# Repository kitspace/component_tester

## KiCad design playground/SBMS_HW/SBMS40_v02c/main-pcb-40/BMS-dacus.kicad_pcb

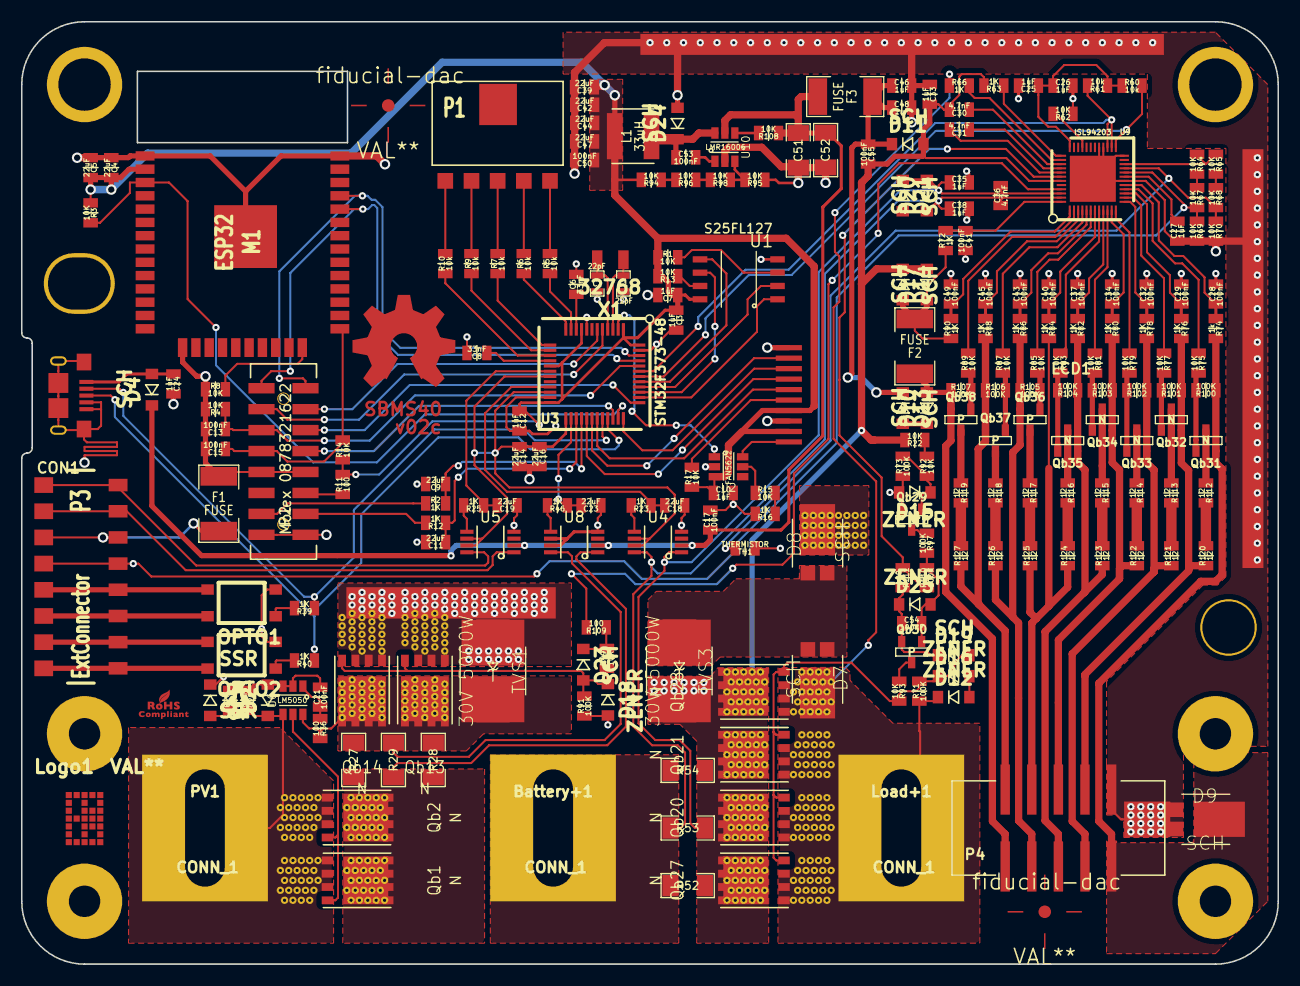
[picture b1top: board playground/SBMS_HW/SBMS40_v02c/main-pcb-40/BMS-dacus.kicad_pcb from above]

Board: 2 copper layers, 120.0 x 90.0 mm, 225 parts (0 on the bottom side), 164 nets.

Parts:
Battery+1: CONN_1; 1PIN_Power-dac-65A2
C1, C2: 22pF; SM0603_Capa
C3, C7, C10, C12, C24, C25, C26, C27, C33, C35, C38, C46, C48: 1uF; SM0805-dac
C4, C5, C9, C11, C14, C16, C18, C19, C23, C39, C42, C44, C47: 22uF; SM0805-dac
C6, C8: 33nF; SM0805-dac
C13, C15, C17, C20, C21, C28, C29, C32, C34, C37, C40, C41, C43, C45, C49, C50, C53, C54, C55: 100nF; SM0805-dac
C30, C31, C36: 4.7nF; SM0805-dac
C51, C52: 10uF; SM1206
CON1: USB-MICRO-B; USB_MICRO_B-2
D1, D2, D4, D10, D11, D13, D14, D17, D19, D20, D21, D23, D24: SCH; Diode-dac3
D7: SCH; SBRT20M80-dac-simple4-D7
D8: SCH; SBRT20M80-dac-simple4-D8
D9: SCH; SBRT20M80-dac-simple4-D9
D12, D15, D16, D18, D25: ZENER; Diode-dac3
F1, F2, F3: FUSE; SM1808-dac
L1: 33uH; 5x5-L1
LCD1: LCD-10pin; LCD-24-10pin
Load+1: CONN_1; 1PIN_Power-dac-65A2
Logo1: VAL**; Logo1
M1: ESP32; ESP32-2
OPTO1, OPTO2: SSR; Opto-dac3
OSHW_COPPER_10MM: VAL**; OSHW_COPPER_10MM
P1: TouchButtons; SIL-5-dac
P2: Molex 0878321622; con_8x2x2mm-dac
P3: ExtConnector; SMD-8-dac1
P4: CellMon; 5x2_SMD-dac
PV1: CONN_1; 1PIN_Power-dac-65A2
Qb1, Qb2, Qb13, Qb14, Qb20, Qb21, Qb27, Qb28: N; PG-TDSON-dac-vias3
Qb29, Qb31, Qb32, Qb33, Qb34, Qb35: N; SOT23-dac-4
Qb30, Qb36, Qb37, Qb38: P; SOT23-dac-4
R1, R3, R4, R8, R13, R14, R15, R17, R22, R62, R64, R65, R67, R68, R69, R70, R75, R77, R79, R81, R83, R85, R87, R89, R92, R93, R94, R95, R96, R98, R99, R108: 10K; SM0805-dac
R2, R12, R16, R20, R23, R25, R39, R40, R46, R63, R66, R72, R76, R78, R80, R82, R84, R86, R88, R90: 1K; SM0805-dac
R5, R6, R7, R9, R10, R60, R61: 10k; SM0805-dac
R11, R36, R109, R111: 100; SM0805-dac
R27, R28, R29, R52, R53, R54: 1mR; SM1206
R71, R73, R91, R97, R100, R101, R102, R103, R104, R105, R106, R107, R110: 100K; SM0805-dac
R74: 1k; SM0805-dac
R112, R113, R114, R115, R116, R117, R118, R119, R120, R121, R122, R123, R124, R125, R126, R127: 12; SM0805-dac
TH1: THERMISTOR; SM0805-dac
TVS1: 30V 5000W; DO-214AB-dac-simple4-TVS1
TVS3: 30V 5000W; DO-214AB-dac-simple4-TVS3
U1: S25FL127; Flash-SO8E-dac2
U2: FAN5622; LM5050-SOT23_6-dac
U3: STM32F373-48; LQFP48-3-dac
U4, U5, U8: LMP8481; LMP8481-SSOP8-dac
U6: LM5050; LM5050-SOT23_6-dac
U9: ISL94203; QFP48-dac-3
U10: LMR16006; LM5050-SOT23_6-dac
X1: 32768; 32khz
fiducial-dac: VAL**; fiducial-dac3
fiducial-dac#2: VAL**; fiducial-dac3

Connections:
/ADC1N: P3.1, U5.8
/ADC1P: P3.2, U5.1
/BAT0: D9.2, P4.2, Qb31.S, R74.2, R100.1
/BAT1: P4.3, Qb32.S, R76.2, R101.1, R120.1
/BAT2: P4.4, Qb33.S, R78.2, R102.1, R121.1
/BAT3: P4.5, Qb34.S, R80.2, R103.1, R122.1
/BAT4: P4.6, Qb35.S, R82.2, R104.1, R123.1
/BAT5: P4.7, R84.2, R124.1, R125.1
/BAT6: P4.8, Qb36.S, R86.2, R105.1, R126.1
/BAT7: P4.9, Qb37.S, R88.2, R106.1, R127.1
/BAT+: D10.1, F2.1, P4.10, Qb38.S, R107.1
/BOOT0: C13.1, P2.5, R4.1, U3.44
/CFET: R109.2, U9.45
/CFET1: D18.2, D23.1, Qb13.G, Qb14.G, R91.2, R99.1
/CPV1P: Qb1.D, Qb2.D, R27.1, R28.1, R29.1, U8.1
/CSI1a: Battery+1.1, C36.1, C38.1, D20.2, D21.1, R52.1, R53.1, R54.1, U4.8, U9.47
/CSI2a: C30.2, C33.2, C35.1, C36.2, C55.2, D11.1, D14.2, D17.1, D18.1, D20.1, D21.2, Qb13.S, Qb14.S, Qb20.D, Qb21.D, Qb27.D, Qb28.D, R22.2, R52.2, R53.2, R54.2, R63.2, R91.1, TVS1.1, TVS3.2, U4.1, U9.43, U9.46
/DFET: R110.1, R111.1, U9.42
/DFET1: D16.2, D19.1, Qb20.G, Qb21.G, Qb27.G, Qb28.G, R71.2, R93.2
/DG1: Qb1.G, Qb2.G, U6.5
/ESPFLASH: C15.1, M1.25, P2.7, R14.2
/ESPRST: M1.3, R3.2, U3.35
/EXTADC1: C19.2, R25.1, U3.18
/EXTADC2: C9.1, R2.2, U3.28
/EXTADC3: C11.1, R12.1, U3.27
/EXTIO1: P2.3, U3.5
/EXTIO2: P2.4, U3.6
/EXTIO3: CON1.2, R39.1, U3.32
/EXTIO4: CON1.3, R40.1, U3.33
/EXTIO5: P2.6, U3.37
/FBAT+: C17.1, C51.1, C52.1, D4.2, F3.2, R108.1, U4.2, U5.2, U8.2, U10.5
/GCB1: Qb31.G, R75.2, R100.2
/GCB2: Qb32.G, R77.2, R101.2
/GCB3: Qb33.G, R79.2, R102.2
/GCB4: Qb34.G, R81.2, R103.2
/GCB5: Qb35.G, R83.2, R104.2
/GCB6: Qb36.G, R85.1, R105.2
/GCB7: Qb37.G, R87.1, R106.2
/GCB8: Qb38.G, R89.1, R107.2
/LCDCS: LCD1.3, U3.36
/LCDDC: LCD1.2, U3.30
/LCDLED: U2.1, U3.2
/LCDSCLK: LCD1.4, U3.29
/LCDSDI: LCD1.5, U3.31
/LDMON: D7.2, D12.2, Load+1.1, Qb20.S, Qb21.S, Qb27.S, Qb28.S, R66.1, R71.1
/PA1: P1.1, R10.2
/PA2: P1.2, R9.2
/PA3: P1.3, R7.2
/PA4: P1.4, R6.2
/PA5: P1.5, R5.2
/PV1: C20.2, D2.2, PV1.1, Qb1.S, Qb2.S, U6.4
/PV+: Qb13.D, Qb14.D, R27.2, R28.2, R29.2, R36.2, TVS1.2, U6.6, U8.8
/SCK: R60.2, U3.42, U9.25
/SDA: R61.2, U3.43, U9.26, U9.27
/SDADC2P: C18.2, R23.1, U3.21
/SDADC38: C23.2, R46.1, U3.26
/SPI1CLK: U1.6, U3.39
/SPI1CS: U1.1, U3.38
/SPI1MISO: U1.2, U3.40
/SPI1MOSI: U1.5, U3.41
/SWD: P2.8, U3.34
/TEMPO: R64.1, R65.1, U9.22
/USARTRX: M1.35, P2.2, U3.46
/USARTTX: M1.34, P2.1, U3.45
/VBATT: C41.1, R72.2, U9.48
/VC0: C28.1, R74.1, U9.17
/VC1: C29.1, R76.1, U9.15
/VC2: C32.1, R78.1, U9.13
/VC3: C34.1, R80.1, U9.11
/VC4: C37.1, R82.1, U9.9
/VC5: C40.1, R84.1, U9.7
/VC6: C43.1, R86.1, U9.5
/VC7: C45.1, R88.1, U9.3
/VC8: C49.1, R90.2, U9.1
/VDD33: C3.1, C4.2, C5.2, C7.1, C10.1, C12.1, C39.1, C42.1, C44.1, C47.1, C50.1, L1.1, LCD1.7, LCD1.9, M1.2, R1.1, R3.1, R11.2, R13.2, R14.1, R17.1, R94.2, U1.8, U2.3, U3.1, U3.9, U3.17, U3.24, U3.48
/VREFSD: C14.1, C16.1, U3.19, U3.22, U3.25, U4.6, U4.7, U5.6, U5.7
/XT1: P3.4, R67.2, R69.1, U9.20
/XT2: R68.2, R70.1, TH1.2, U9.21
GND: C1.2, C2.1, C3.2, C4.1, C5.1, C6.2, C7.2, C8.2, C9.2, C10.2, C11.2, C12.2, C13.2, C14.2, C15.2, C16.2, C17.2, C18.1, C19.1, C23.1, C24.2, C25.2, C26.2, C27.1, C28.2, C29.2, C32.2, C33.1, C34.2, C35.2, C37.2, C38.2, C39.2, C40.2, C41.2, C42.2, C43.2, C44.2, C45.2, C46.2, C47.2, C48.2, C49.2, C50.2, C51.2, C52.2, CON1.4, CON1.5, CON1.6, CON1.7, CON1.8, CON1.9, D1.2, D8.2, D9.1, D15.1, D24.1, F1.1, LCD1.1, LCD1.8, M1.1, M1.15, M1.38, M1.39, OPTO1.2, OPTO2.2, P2.9, P2.10, P2.15, P2.16, P4.1, Qb29.S, R4.2, R8.1, R16.2, R62.1, R69.2, R70.2, R73.1, R95.1, TH1.1, U1.4, U2.2, U3.8, U3.23, U3.47, U4.4, U5.4, U8.4, U8.6, U8.7, U9.0, U9.18, U9.24, U9.28, U9.29, U10.2
unnamed: C1.1, U3.3, X1.2
unnamed: C2.2, U3.4, X1.1
unnamed: C6.1, U3.10
unnamed: C8.1, U3.16
unnamed: C20.1, C21.2, D2.1, R20.2, U6.2, U6.3
unnamed: C21.1, R36.1, U6.1
unnamed: C24.1, CON1.1, D4.1
unnamed: C25.1, C26.1, R60.1, R61.1, U9.36
unnamed: C27.2, U9.19
unnamed: C30.1, U9.39
unnamed: C31.1, U9.40
unnamed: C31.2, U9.41
unnamed: C46.1, C48.1, C55.1, D11.2, D13.2, F3.1
unnamed: C53.1, D24.2, L1.2, U10.6
unnamed: C53.2, U10.1
unnamed: C54.1, D19.2, D25.2, Qb30.S, R111.2
unnamed: C54.2, D25.1, Qb30.G, R97.2, R110.2
unnamed: D1.1, R20.1
unnamed: D7.1, D8.1, TVS3.1
unnamed: D10.2, D13.1
unnamed: D12.1, D16.1
unnamed: D14.1, D17.2, F2.2, R72.1, R90.1
unnamed: D15.2, Qb29.G, R73.2, R92.1
unnamed: D23.2, R99.2, R109.1
unnamed: F1.2, P3.3
unnamed: LCD1.6, R17.2
unnamed: LCD1.10, U2.6
unnamed: M1.24, R8.2
unnamed: OPTO1.1, R39.2
unnamed: OPTO1.3, P3.5
unnamed: OPTO1.4, P3.6
unnamed: OPTO2.1, R40.2
unnamed: OPTO2.3, P3.7
unnamed: OPTO2.4, P3.8
unnamed: P2.12, R11.1
unnamed: P2.13, R2.1
unnamed: P2.14, R12.2
unnamed: Qb29.D, R97.1
unnamed: Qb30.D, R93.1
unnamed: Qb31.D, R112.1
unnamed: Qb32.D, R113.1
unnamed: Qb33.D, R114.1
unnamed: Qb34.D, R115.1
unnamed: Qb35.D, R116.1
unnamed: Qb36.D, R117.1
unnamed: Qb37.D, R118.1
unnamed: Qb38.D, R119.1
unnamed: R1.2, U1.3
unnamed: R5.1, U3.11
unnamed: R6.1, U3.12
unnamed: R7.1, U3.13
unnamed: R9.1, U3.14
unnamed: R10.1, U3.15
unnamed: R13.1, U1.7
unnamed: R15.1, U2.5
unnamed: R15.2, R16.1
unnamed: R22.1, R92.2
unnamed: R23.2, U4.5
unnamed: R25.2, U5.5
unnamed: R46.2, U8.5
unnamed: R62.2, U9.33
unnamed: R63.1, U9.37
unnamed: R64.2, R67.1
unnamed: R65.2, R68.1
unnamed: R66.2, U9.38
unnamed: R75.1, U9.16
unnamed: R77.1, U9.14
unnamed: R79.1, U9.12
unnamed: R81.1, U9.10
unnamed: R83.1, U9.8
unnamed: R85.2, U9.6
unnamed: R87.2, U9.4
unnamed: R89.2, U9.2
unnamed: R94.1, R96.2
unnamed: R95.2, R98.1, U10.3
unnamed: R96.1, R98.2
unnamed: R108.2, U10.4
unnamed: R112.2, R120.2
unnamed: R113.2, R121.2
unnamed: R114.2, R122.2
unnamed: R115.2, R123.2
unnamed: R116.2, R124.2
unnamed: R117.2, R125.2
unnamed: R118.2, R126.2
unnamed: R119.2, R127.2

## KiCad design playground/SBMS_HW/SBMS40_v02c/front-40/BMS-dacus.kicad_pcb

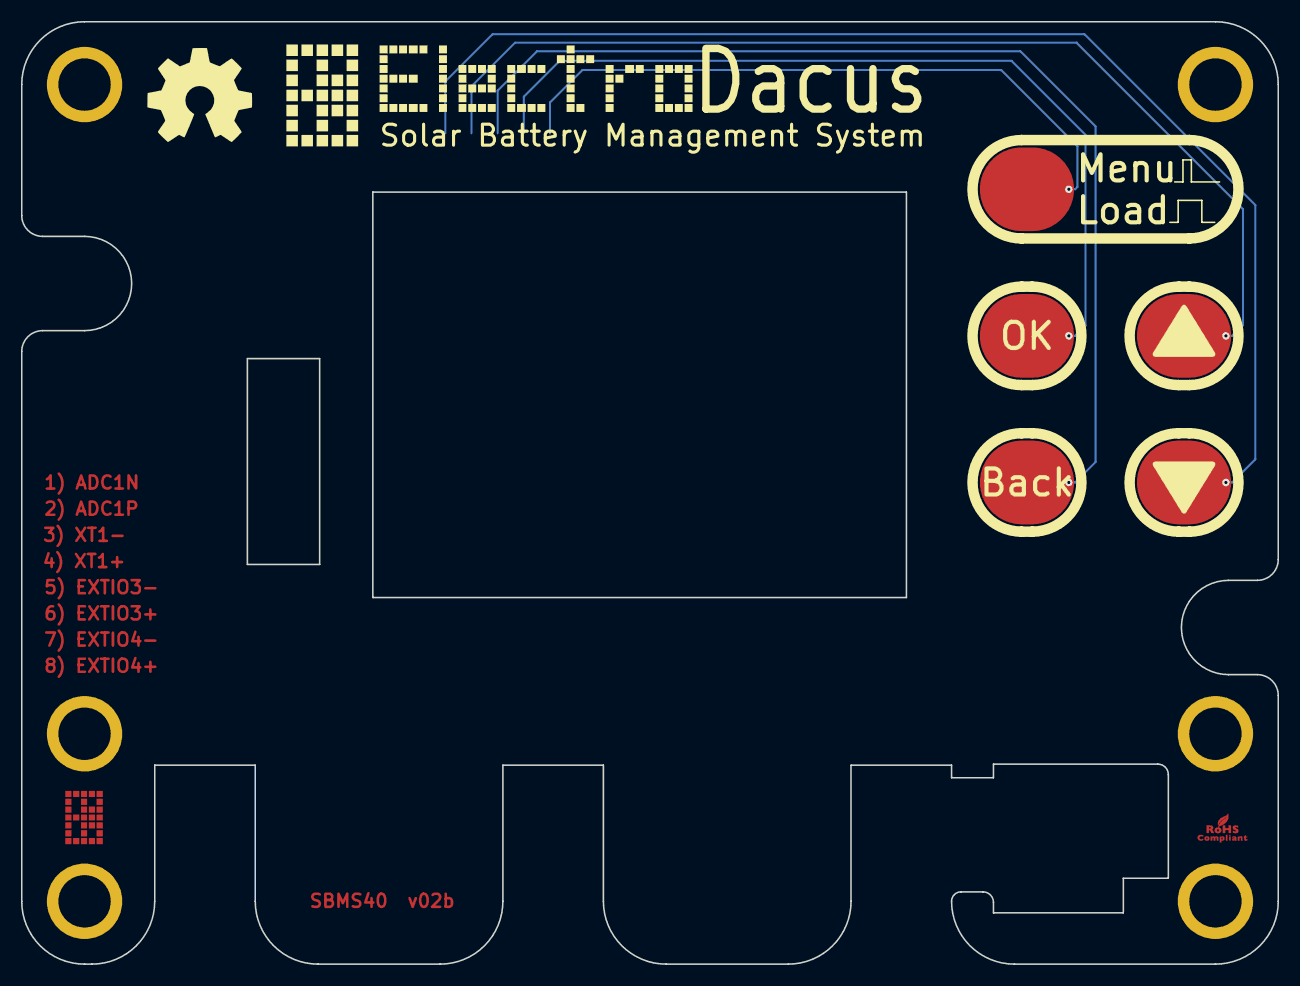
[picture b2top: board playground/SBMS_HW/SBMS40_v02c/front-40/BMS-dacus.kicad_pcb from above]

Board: 2 copper layers, 120.0 x 90.0 mm, 11 parts (0 on the bottom side), 5 nets.

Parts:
BA1, BA2, BA3, BA4, BA5: CONN_1; button_SMD-dac-40
Logo1: VAL**; Logo1
PA1, PA2, PA3, PA4, PA5: CONN_1; button_contact_SMD-dac3

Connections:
unnamed: BA1.1, PA1.1
unnamed: BA2.1, PA2.1
unnamed: BA3.1, PA3.1
unnamed: BA4.1, PA4.1
unnamed: BA5.1, PA5.1

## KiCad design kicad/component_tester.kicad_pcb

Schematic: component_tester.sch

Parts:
DRAWING101: DRAWING; combined

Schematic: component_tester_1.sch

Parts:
BAT201: CR2032; Battery_Retainer_2032_BK-912
C201: 10uF; C_0805
C202: 100n; C_0402
C203, C207: 47u; C_0805
C204, C205: 22p; C_0201
C206: 1n; C_0201
C208, C209, C210, C211, C212, C213: V 3p; C_0201
D201: BAV99; SOT-523; MPN1 BAV99T-7-F
D203: BAS40; LED_0402; MPN BAS40LP-7
DRAWING201: DRAWING; pads
DRAWING202: DRAWING; pads_bottom
IC201: MCP1640; SOT23-6
IC202: ATmega328P-MMH; QFN-28-1EP_4x4mm_Pitch0.4mm
L201: 4.7uH; R_0603
Q201: 8 MHz; NDK-NX3225GA_xtal
R201, R202, R203, R205, R210, R211, R212, R213: 10k; R_0201
R204: 1M; R_0201
R206: 750k; R_0201
R207: 240k; R_0201
R209: 330k; R_0201
R214, R216, R218: 680; R_0201
R215, R217, R219: 470k; R_0201
SW201: EVQ; PANASONIC_EVQ
T201: PMV65XP; SOT23
T202: BSS84; SOT23
T203: BSS123; SOT-323_SC-70; MPN BSS123W-7-F
T204: BC847; SOT-523; MPN BC847AT-7-F
X201: MICRO-USB; TE_1981568-1
X202: ISP; Pin_Header_Straight_2x03_Pitch1.27mm

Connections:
+5V: C201.1, C202.2, C207.1, IC201.5, IC202.3 (VCC), IC202.16 (AVCC), R202.2, R206.2, R211.2, X202.2; also elsewhere on the board
+BATT: BAT201.1, T201.3; also elsewhere on the board
/component_tester_1/~RESET: IC202.25 (~RESET~/PC6), R202.1, X202.5
GND: BAT201.2, C201.2, C202.1, C203.2, C204.1, C205.1, C206.1, C207.2, C208.2, C209.2, C210.2, C211.2, C212.2, C213.2, IC201.2, IC202.4 (GND), IC202.18 (GND), IC202.29 (GND), R201.1, R203.1, R207.2, R209.1, R210.2, R212.1, T203.2, T204.2, X201.5, X202.6; also elsewhere on the board
unnamed: C203.1, D201.2, IC201.6, L201.1, R204.2, R205.2, SW201.1, SW201.2, T201.2, T202.2
unnamed: C204.2, IC202.6 (XTAL2/PB7), Q201.2
unnamed: C205.2, IC202.5 (XTAL1/PB6), Q201.1
unnamed: C206.2, IC202.17 (AREF)
unnamed: C208.1, C211.1, DRAWING201.1, DRAWING202.1, IC202.19 (PC0), R214.2, R215.2
unnamed: C209.1, C212.1, DRAWING201.2, DRAWING202.2, IC202.20 (PC1), R216.2, R217.2
unnamed: C210.1, C213.1, DRAWING201.3, DRAWING202.3, IC202.21 (PC2), R218.2, R219.2
unnamed: D203.1, R210.1, SW201.3, SW201.4, T203.1
unnamed: IC202.8 (PD6), R212.2, R213.2
unnamed: IC201.1, L201.2
unnamed: IC201.3, R203.2, T202.3
unnamed: IC201.4, R206.1, R207.1
unnamed: IC202.9 (PD7), R211.1, T203.3
unnamed: IC202.10 (PB0), R214.1
unnamed: IC202.11 (PB1), R215.1
unnamed: IC202.12 (PB2), R216.1
unnamed: IC202.13 (PB3), R217.1, X202.4
unnamed: IC202.14 (PB4), R218.1, X202.1
unnamed: IC202.15 (PB5), R219.1, X202.3
unnamed: IC202.24 (PC5), R204.1, R209.2
unnamed: R205.1, T202.1, T204.3
unnamed: R213.1, T204.1
SEROUT: IC202.22 (PC3); also elsewhere on the board
SUP_UART: D201.3; also elsewhere on the board
USBDM: X201.2; also elsewhere on the board
USBDP: X201.3; also elsewhere on the board
VCC: D201.1, R201.2, T201.1, X201.1; also elsewhere on the board

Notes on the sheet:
Knopfzelle
CR2032
Supply-Netze:
+5V = Spannungsregler-Ausgang
VCC = 5V vom USB
VI = Spannungsregler-Eingang
+BATT = 3V von Lithiumzelle
K.-H. Kübbeler, DF3DCB, DH8GHH

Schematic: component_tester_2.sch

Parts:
C301: 100n; C_0805
C302, C303: 4,7u; C-TAN_A
IC301: FT232RL; SSOP28
IC302: MAX1811; SO08
J301, J302: 0R-JUMPA; A0R-JMP
LED301: LEDCHIP-LED0805; CHIP-LED0805
R301: 100; R_0402
T301: BSS123; SOT23

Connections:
+BATT: C302.+, IC302.5; also elsewhere on the board
GND: C301.1, C302.-, C303.-, IC301.7, IC301.18, IC301.21, IC301.25, IC301.26, IC302.2, IC302.3, IC302.6, J302.3; also elsewhere on the board
unnamed: IC301.5, T301.2
unnamed: IC302.7, J302.2
unnamed: IC302.8, LED301.C
unnamed: LED301.A, R301.2
SEROUT: T301.3; also elsewhere on the board
SUP_UART: C301.2, IC301.4, IC301.20; also elsewhere on the board
USBDM: IC301.16; also elsewhere on the board
USBDP: IC301.15; also elsewhere on the board
VCC: C303.+, IC302.4, J301.2, J302.1, R301.1, T301.1; also elsewhere on the board

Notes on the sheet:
Option USB-Ausgabe
Option Li+ Charger

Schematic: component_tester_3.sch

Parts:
C403: 10uF; C_0805
C404, C406, C407, C408: 1uF; C_0603
C405: 2.2uF/16V; C_0603
D401, D402, D403: 1N4148; SOD-323
OLED1: Conn_01x30; SSD1306
Q401, Q402: BSS138; SOT23-WIDE
R401, R402, R403, R404, R405, R406, R407, R408: 10K; R_0201
R409: 390K; R_0201

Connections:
+5V: R403.2, R404.2; also elsewhere on the board
+BATT: C407.2, C408.2, OLED1.6, OLED1.9, Q401.1, Q402.1, R401.2, R402.2, R405.2, R406.2, R407.2; also elsewhere on the board
/component_tester_3/CS_3.3V: D401.A, OLED1.13, R405.1
/component_tester_3/CS_5.0V: D401.C
/component_tester_3/D0/SCLK/SCK_3.3V: OLED1.18, Q402.2, R402.1
/component_tester_3/D0/SCLK/SCK_5.0V: Q402.3, R404.1
/component_tester_3/D1/MOSI/SDA1_3.3V: OLED1.19, Q401.2, R401.1
/component_tester_3/D1/MOSI/SDA_5.0V: Q401.3, R403.1
/component_tester_3/DC/SA0_3.3V: D403.A, OLED1.15, R407.1
/component_tester_3/DC/SA0_5.0V: D403.C
/component_tester_3/RST_3.3V: D402.A, OLED1.14, R406.1
/component_tester_3/RST_5.0V: D402.C
GND: C403.1, C405.1, C407.1, C408.1, OLED1.1, OLED1.8, OLED1.10, OLED1.12, OLED1.29, OLED1.30, R408.1, R409.1; also elsewhere on the board
unnamed: C403.2, OLED1.28
unnamed: C404.1, OLED1.5
unnamed: C404.2, OLED1.4
unnamed: C405.2, OLED1.27
unnamed: C406.1, OLED1.3
unnamed: C406.2, OLED1.2
unnamed: OLED1.11, R408.2
unnamed: OLED1.26, R409.2

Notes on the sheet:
= 011110+SA0+RW
= 0x7A with DC/SA0_5.0V floating/high
= 0x78 with DC/SA0_5.0V at GND
I2C Address

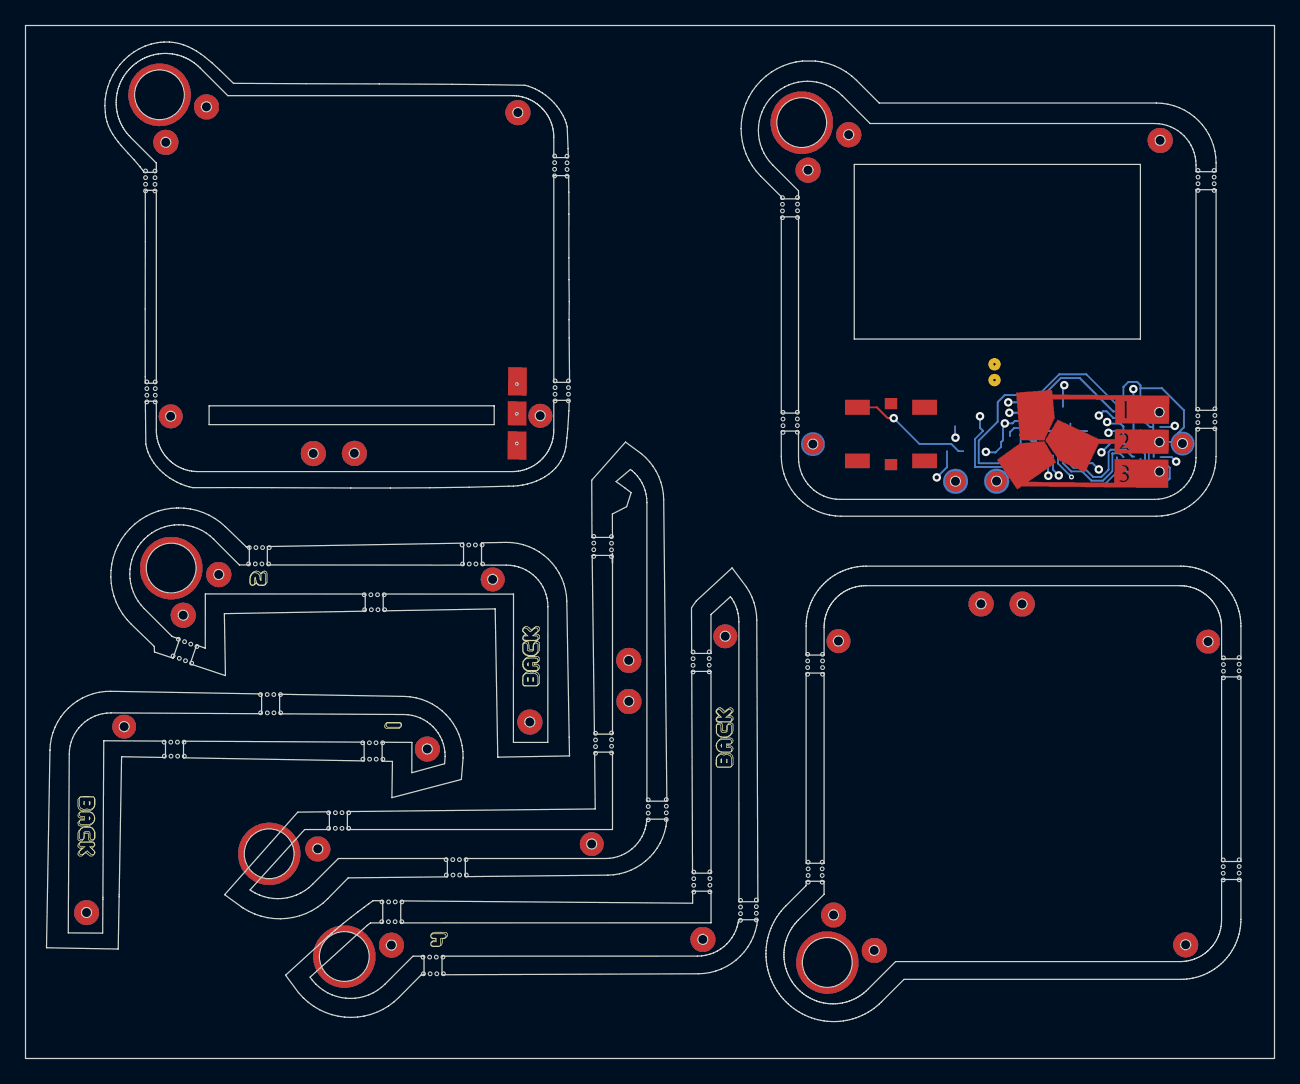
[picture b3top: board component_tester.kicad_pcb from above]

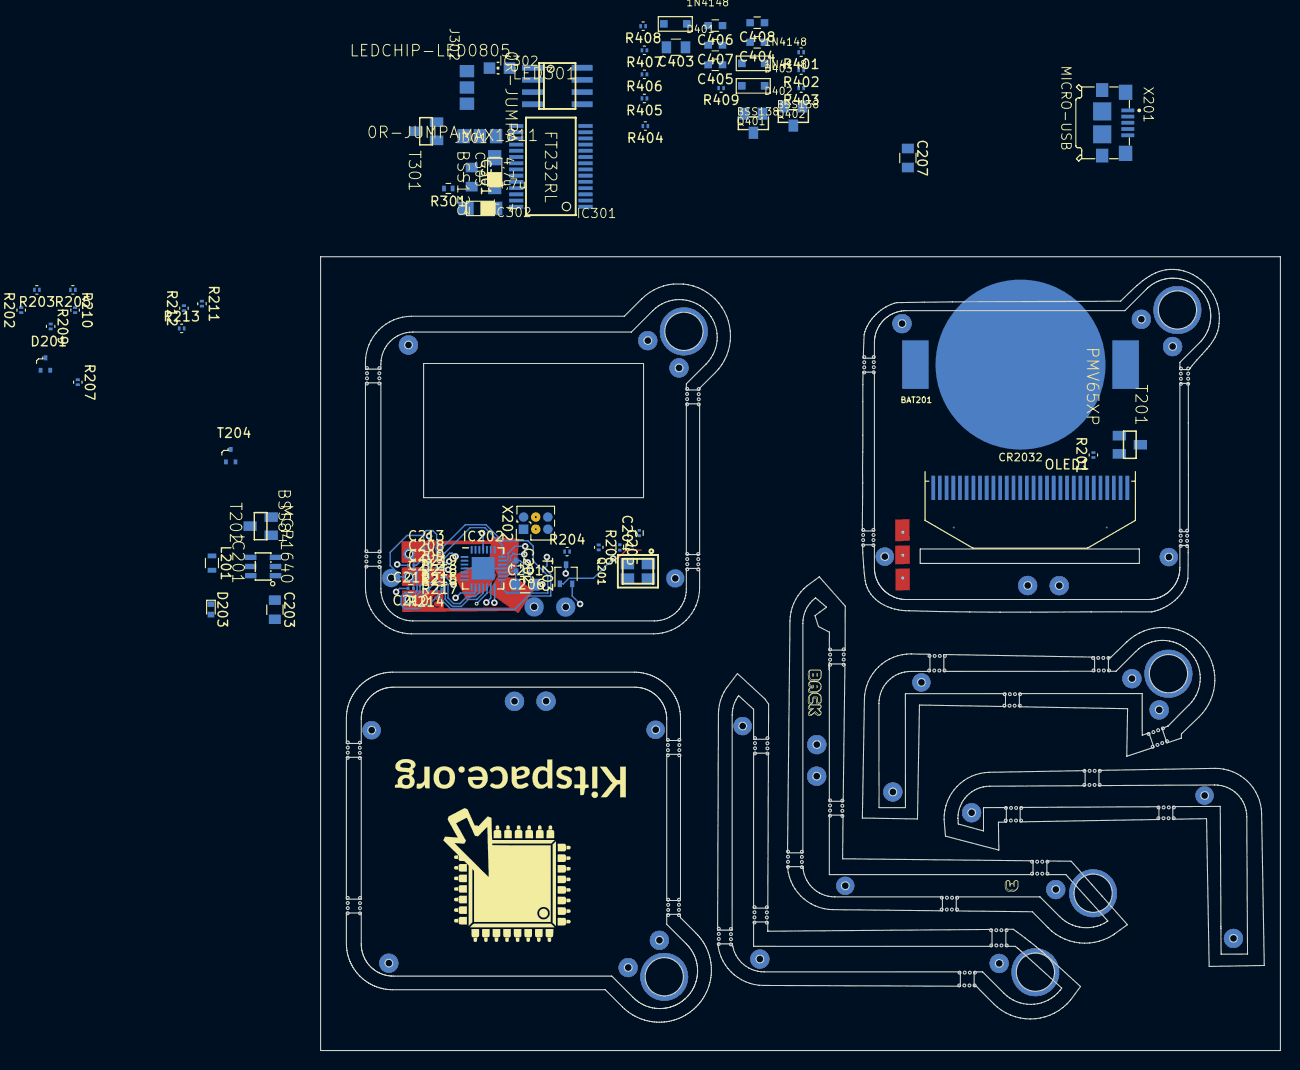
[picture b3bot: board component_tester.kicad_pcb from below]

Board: 4 copper layers, 100.4 x 83.0 mm, 79 parts (75 on the bottom side), 50 nets.

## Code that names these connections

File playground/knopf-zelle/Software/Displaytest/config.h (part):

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#define ADC_PORT PORTC
#define ADC_DDR DDRC
#define ADC_PIN PINC
#define TP1 PC0
#define TP2 PC1
#define TP3 PC2
// Port pin for external Voltage measurement (zener voltage extension)
#define TPext PC3
// Port pin for 2.5V precision reference used for VCC check (optional)
#define TPREF PC4
// Port pin for Battery voltage measuring
#define TPBAT PC5

// setting for voltage devider of Batterie voltage measurement 10K and 3.3k
#ifndef BAT_NUMERATOR
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#define ON_DDR DDRD
#define ON_PORT PORTD
#define ON_PIN_REG PIND
#define ON_PIN PD6      //Pin, must be switched to high to switch power on

#ifdef STRIP_GRID_BOARD
// Strip Grid board version
#define RST_PIN PD0     //Pin, is switched to low, if push button is pressed
#else
// normal layout version
#define RST_PIN PD7     //Pin, is switched to low, if push button is pressed
#endif


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*/
//#define SWUART_INVERT

#define TxD PC3	//TxD-Pin of Software-UART; must be at Port C !
#ifdef WITH_UART
 #define TXD_MSK (1<<TxD)
#else
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
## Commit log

2018-04-19 Work on schematic
2018-04-19 Schema schemaaa
2018-04-19 Move hardware into kicad dir
2018-04-19 Add software
2018-04-19 Run clang-format on software
2018-04-26 Work on svg
2018-04-27 Work on drawings
2018-04-27 Start panelizing
2018-04-28 Work on panelization
2018-04-28 Work on drills
2018-04-28 Panelize the whole thing, rat-bites and all
2018-04-28 Start working on pads
2018-04-28 Try out button and add logo
2018-06-09 Adjust logo url
2018-06-09 Adjust logo text some more
2018-06-09 Import eagle project from o28 fifi bauteiltester
2018-06-09 Add drawings back into pcb
2018-06-10 Fix some schematic eagle import oddities
2018-06-11 Add .bak and .bck to gitignore
2018-06-13 Switch resistors and caps to 0201 where possible
2018-06-14 Switch atemega to smaller footprint
2018-06-14 Switch battery holder footprint
2018-06-14 Add OLED footprint
2018-06-14 Add test pads bottom footprint
2018-06-14 Connect up test pads
2018-06-14 Sort out ground net
2018-06-14 Remove all the ground labels and zones
2018-06-14 Remove all vias
2018-06-14 Sort out power nets/labels
2018-06-15 Import Adafruit OLED breakout
2018-06-15 Switch 0201 footprints for 0402
2018-06-15 Switch out crystal oscillator footprint
2018-06-15 Switch button footprint
2018-06-15 Flip the board and begin placing
2018-06-15 Use hierplace to re-arrange footprints
2018-06-15 Continue placing
2018-06-15 Change USB footprint
2018-06-15 Reduce atmega decoupling cap to 10uF
2018-06-15 Use panasonic evq for tactile switch
2018-06-15 Work on placement
2018-06-15 Make all schematic references and values visible
2018-06-15 Remove unnecessary stuff from OLED circuitry
2018-06-15 Add drawings of inner edges to help with layout
2018-06-16 Adjust pads placement tonot interfere with screen
2018-06-16 Work on placing components
2018-06-16 Switch back to 0201s and continue placing
2018-06-16 Set up design rules and test out routing a bit
2018-06-16 Do some routing
2018-06-16 Make ISP header a pogo pin one
2018-06-17 Adjust layers, make sure ISP through holes have copper
2018-06-17 Work on placing/routing
2018-06-17 Cut out precision voltage reference
2018-06-17 Switch some transistors for smaller footprints
2018-06-17 Route some more
2018-06-19 Place and route
2018-06-19 Route stuff
2018-10-08 Remove all kicad-4 schematic libs
2018-10-08 Remove tags from eagle exported footprints
2020-09-11 Add datasheets and playground directories

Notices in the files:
playground/SBMS_HW/SBMS40_v02c/front-40/BMS-dacus.kicad_pcb:
Electrodacus (Schematic and PCB layout released under CC-BY-SA 3.0 licence)
playground/knopf-zelle/Software/Displaytest/config.h:
CC0 defines the capacity of empty terminal pins 1 & 3 without cable
define CC0 36
define C_NULL CC0+CABLE_CAP+(COMP_SLEW1 / (CC0 + CABLE_CAP + COMP_SLEW2))
define CC0 27
